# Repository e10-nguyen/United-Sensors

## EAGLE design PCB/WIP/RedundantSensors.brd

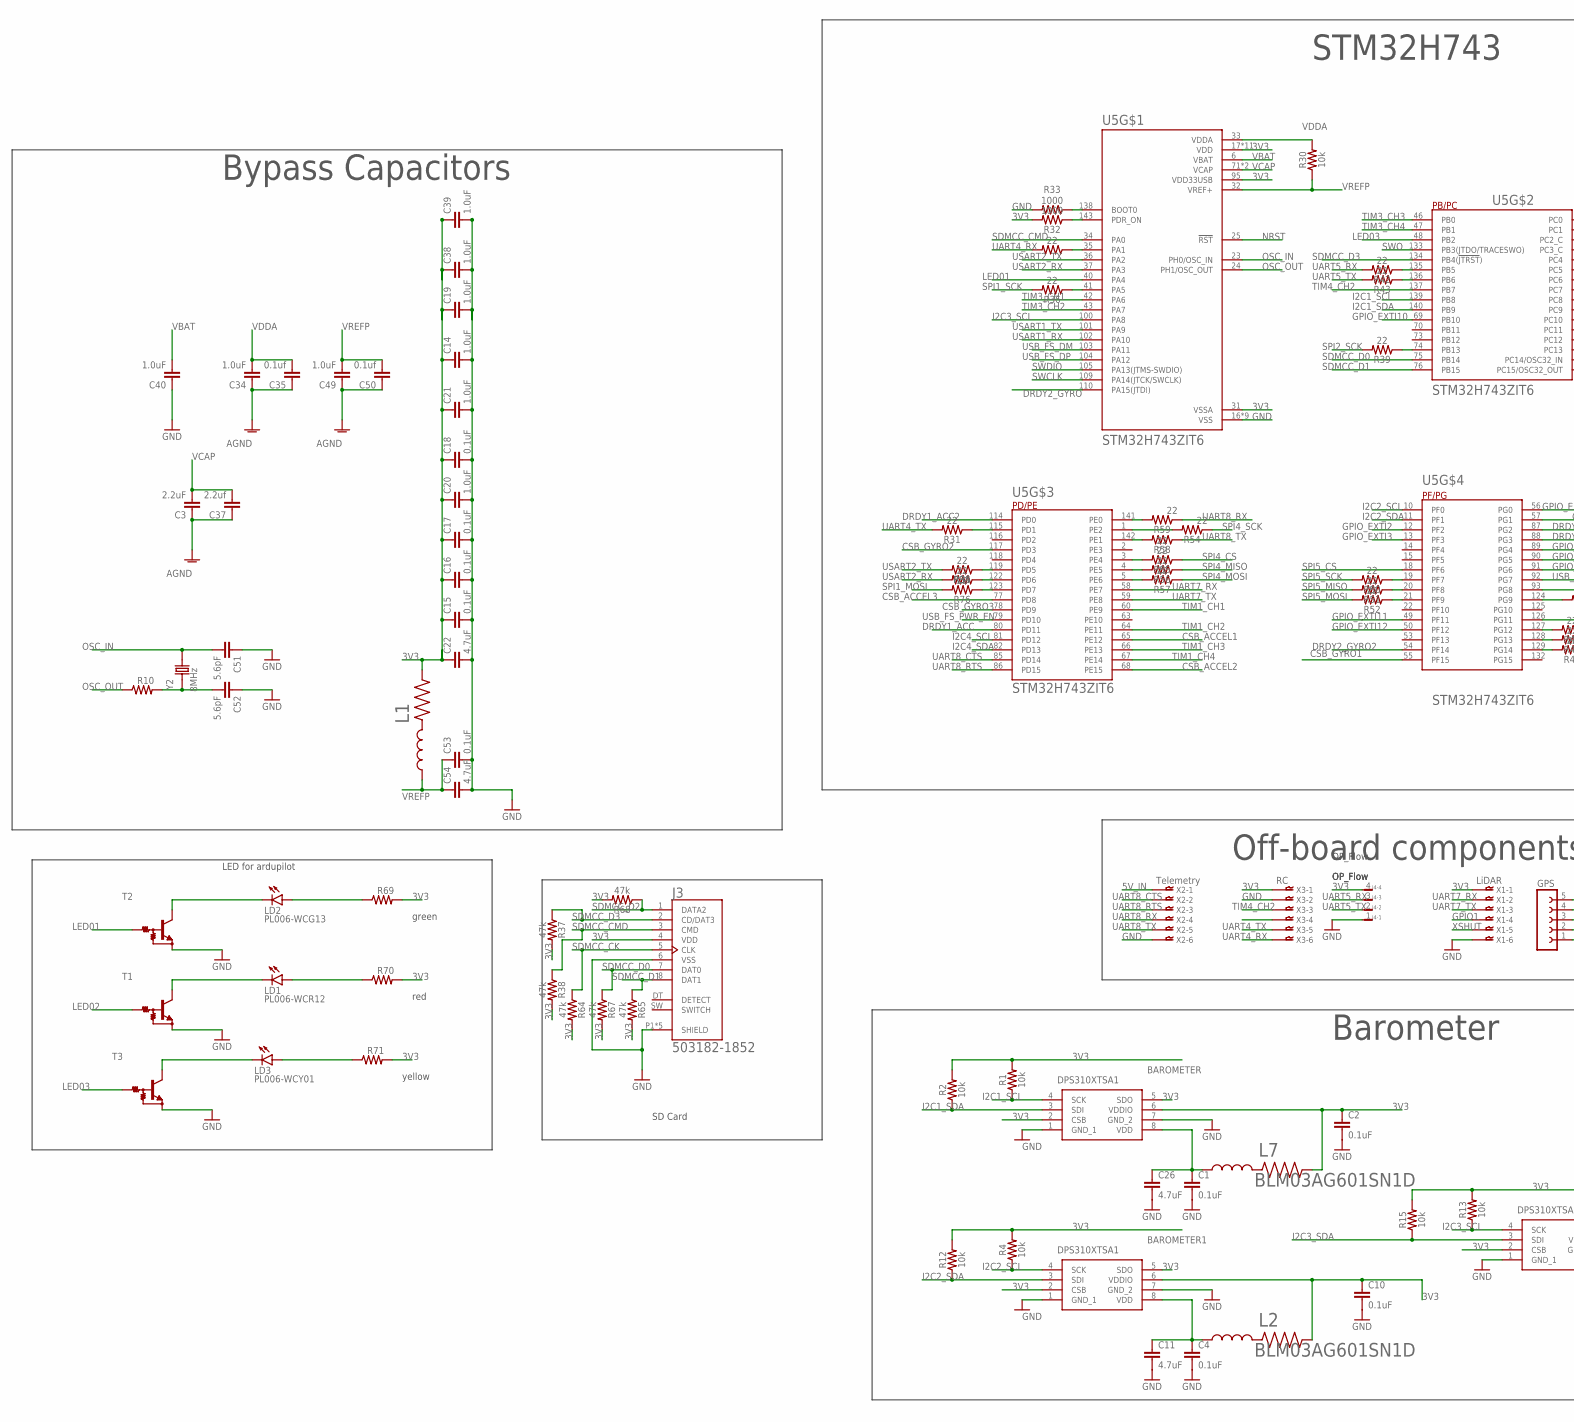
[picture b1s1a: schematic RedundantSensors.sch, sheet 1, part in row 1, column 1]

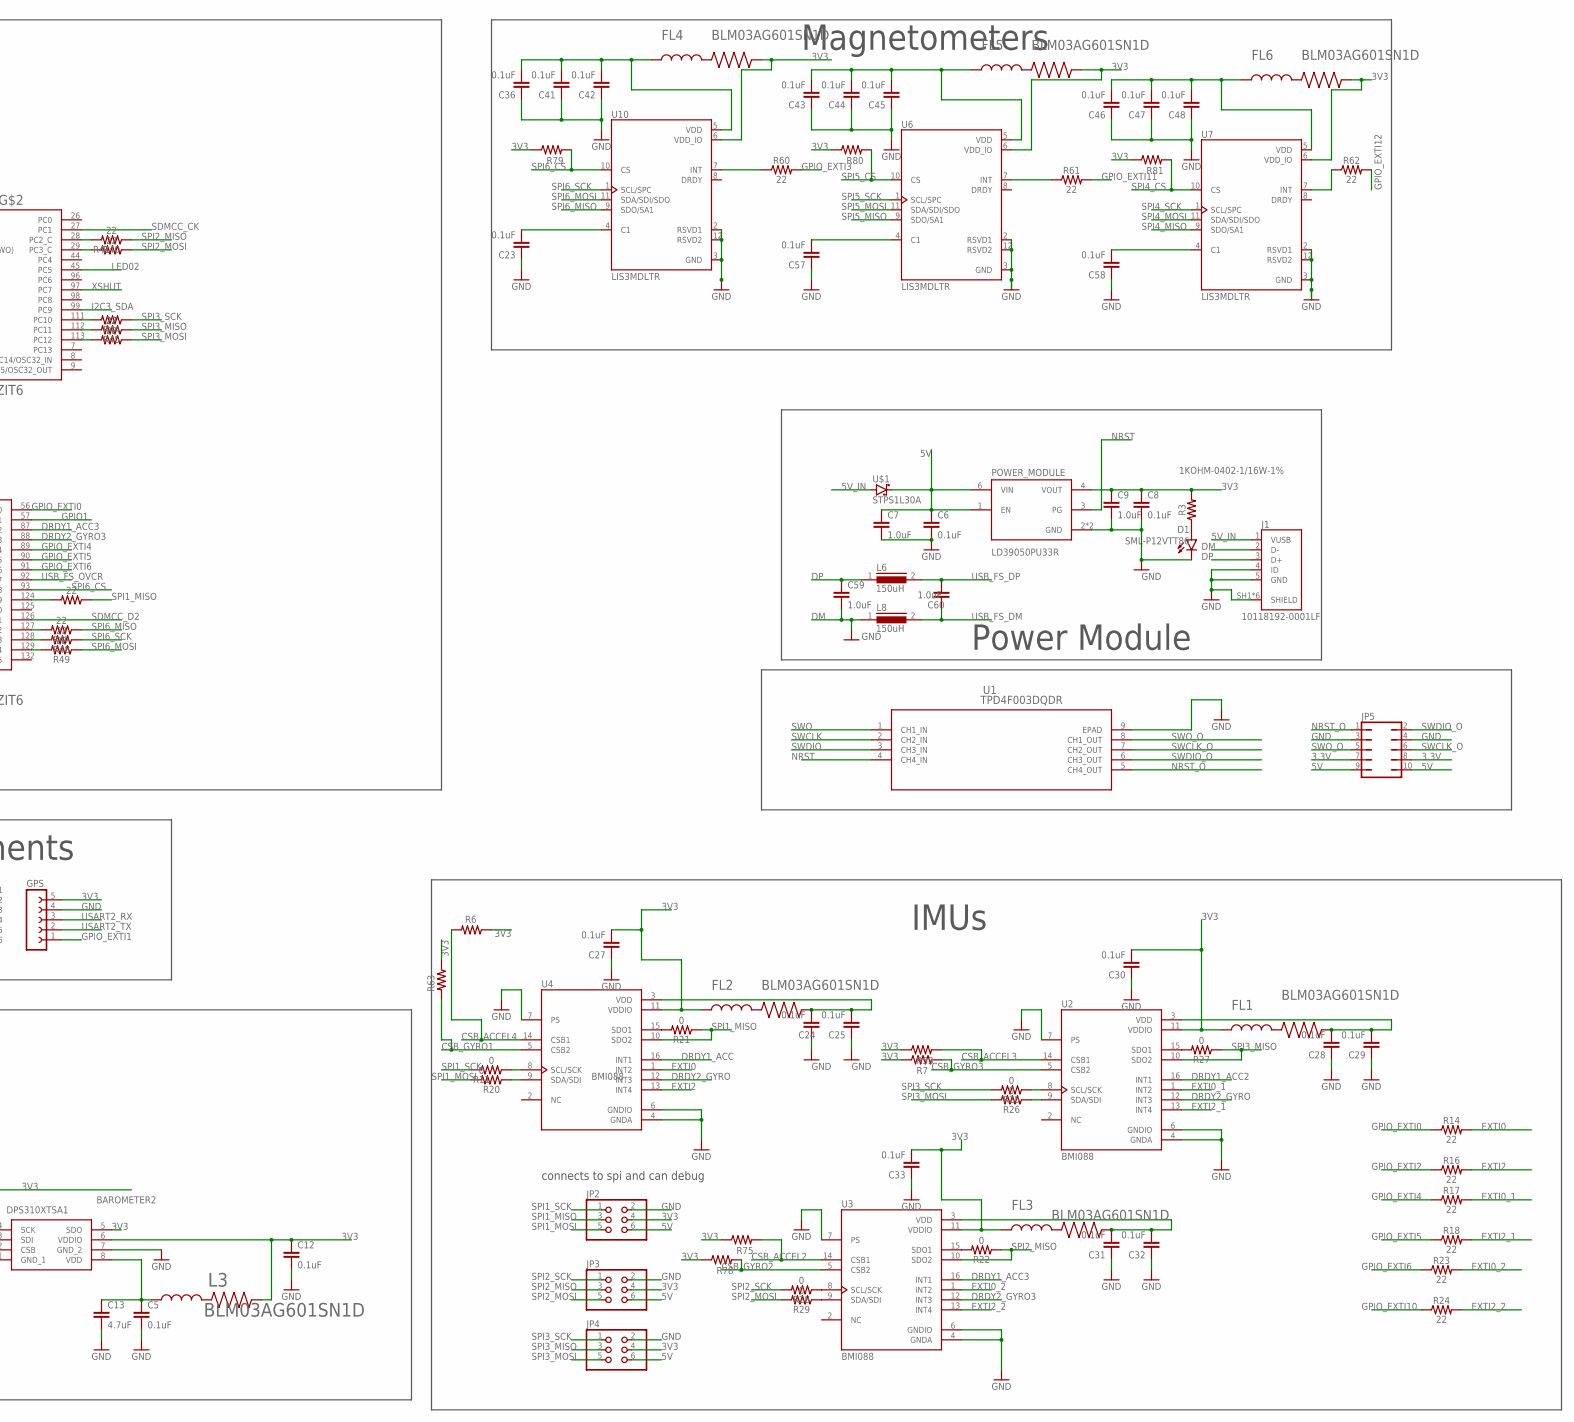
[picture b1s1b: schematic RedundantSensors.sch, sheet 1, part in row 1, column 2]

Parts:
BAROMETER, BAROMETER1, BAROMETER2: DPS310XTSA1
C1, C2, C4, C5, C6, C8, C10, C12: 0.1uF; 0402
C3: 2.2uF; 0805
C7, C9, C59, C60: 1.0uF; 0402
C11, C13, C22, C26, C54: 4.7uF; 0603
C14, C19, C20, C21, C34, C38, C39, C40, C49: 1.0uF; 0805
C15, C16, C17, C18, C23, C24, C25, C27, C28, C29, C30, C31, C32, C33, C36, C41, C42, C43, C44, C45, C46, C47, C48, C53, C57, C58: 0.1uF; 0603
C35, C50: 0.1uf; 0805
C37: 2.2uf; 0805
C51, C52: 5.6pF; 0805
D1: SML-P12VTT86; LED_SML-P11UTT86R
FL1, FL2, FL3, FL4, FL5, FL6: BLM03AG601SN1D; BEADC0603X33N
GPS: FE05-1
J1: 10118192-0001LF; AMPHENOL_10118192-0001LF
J3: 503182-1852; MOLEX_503182-1852
J4: JST-SH-4_SMT_V; BM04B-SRSS-TB
JP2, JP3, JP4: PINHD-2X3; 2X03
JP5: JP5Q
L1, L2, L3, L7: BLM03AG601SN1D; BEADC0603X33N
L6, L8: 150uH; MICC10
LD1: PL006-WCR12; SOT23
LD2: PL006-WCG13; SOT23
LD3: PL006-WCY01; SOT23
POWER_MODULE: LD39050PU33R; SON95P300X300X100-7N
R1, R2, R4, R12, R13, R15, R30: 10k; 0402
R3: 1KOHM-0402-1/16W-1%; 0402
R5, R14, R16, R17, R18, R23, R24, R31, R34, R35, R36, R39, R40, R41, R42, R43, R44, R45, R46, R47, R48, R49, R50, R51, R52, R54, R55, R56, R57, R58, R59, R60, R61, R62, R76, R77: 22; 0402
R6, R7, R53, R63, R75, R78, R79, R80, R81: 10K; RESC1005X35N
R10: 220; RESC1005X35N
R11, R20, R21, R22, R25, R26, R27, R28, R29: 0; 0402
R32, R33: 1000; 0402
R37, R38, R64, R65, R67, R68: 47k; 0402
R69, R70, R71: 270; RESC1005X35N
T1, T2, T3: MUN2213T1-NPN_DRIVER-SC59-BEC; SC59-BEC
U1: TPD4F003DQDR; DQD8_1P2X0P4
U2, U3, U4: BMI088; PQFN50P450X300X100-16N
U5: STM32H743ZIT6; QFP50P2200X2200X160-144N
U6, U7, U10: LIS3MDLTR; XDCR_LIS3MDLTR
U$1: STPS1L30A; DIOM5226X223N
X1: LiDAR; 6FLZ-SM
X2: Telemetry; 6FLZ-SM
X3: RC; 6FLZ-SM
Y2: 8MHz; XTAL_ABLS-8.000MHZ-B2-T

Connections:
3.3V: JP5.7, JP5.8
3V2: C28.2, C29.2, FL1.2, U2.3 (VDD)
3V3: BAROMETER.2 (CSB), BAROMETER.5 (SDO), BAROMETER.6 (VDDIO), BAROMETER1.2 (CSB), BAROMETER1.5 (SDO), BAROMETER1.6 (VDDIO), BAROMETER2.2 (CSB), BAROMETER2.5 (SDO), BAROMETER2.6 (VDDIO), C2.1, C8.1, C9.1, C10.1, C12.1, C14.1, C15.1, C16.1, C17.1, C18.1, C19.1, C20.1, C21.1, C22.1, C27.2, C30.2, C33.2, C38.1, C39.1, FL1.1, FL2.1, FL3.1, FL4.2, FL5.2, FL6.2, GPS.5, J3.4 (VDD), J4.4, JP2.4, JP3.4, JP4.4, L1.2, L2.2, L3.2, L7.2, POWER_MODULE.4 (VOUT), R1.2, R2.2, R3.2, R4.2, R6.1, R7.1, R12.2, R13.2, R15.2, R32.2, R37.2, R38.2, R53.1, R63.1, R64.2, R65.2, R67.2, R68.2, R69.2, R70.2, R71.2, R75.1, R78.1, R79.1, R80.1, R81.1, U2.11 (VDDIO), U3.11 (VDDIO), U4.11 (VDDIO), U5.17 (VDD), U5.30 (VDD), U5.31 (VSSA), U5.39 (VDD), U5.52 (VDD), U5.62 (VDD)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
3V4: C24.2, C25.2, FL2.2, U4.3 (VDD)
3V5: C31.2, C32.2, FL3.2, U3.3 (VDD)
5V: C6.1, C7.1, JP2.6, JP3.6, JP4.6, JP5.9, JP5.10, POWER_MODULE.1 (EN), POWER_MODULE.6 (VIN), U$1.1 (C)
5V_IN: J1.1 (VUSB), U$1.2 (A), X2.1
AGND: C3.1, C34.1, C35.1, C37.1, C49.1, C50.1
CSB_ACCEL1: U5.65 (PE12)
CSB_ACCEL2: R75.2, U3.14 (CSB1), U5.68 (PE15)
CSB_ACCEL3: R53.2, U2.14 (CSB1), U5.77 (PD8)
CSB_ACCEL4: R6.2, U4.14 (CSB1)
CSB_GYRO1: R63.2, U4.5 (CSB2), U5.55 (PF15)
CSB_GYRO2: R78.2, U3.5 (CSB2), U5.117 (PD3)
CSB_GYRO3: R7.2, U2.5 (CSB2), U5.78 (PD9)
DM: C59.2, J1.2 (D-), L8.1
DP: C59.1, J1.3 (D+), L6.1
DRDY1_ACC: U4.16 (INT1), U5.80 (PD11)
DRDY1_ACC2: U2.16 (INT1), U5.114 (PD0)
DRDY1_ACC3: U3.16 (INT1), U5.87 (PG2)
DRDY2_GYRO: U2.12 (INT3), U4.12 (INT3), U5.110 (PA15(JTDI))
DRDY2_GYRO2: U5.54 (PF14)
DRDY2_GYRO3: U3.12 (INT3), U5.88 (PG3)
EXTI0: R14.2, U4.1 (INT2)
EXTI0_1: R17.2, U2.1 (INT2)
EXTI0_2: R23.2, U3.1 (INT2)
EXTI2: R16.2, U4.13 (INT4)
EXTI2_1: R18.2, U2.13 (INT4)
EXTI2_2: R24.2, U3.13 (INT4)
GND: BAROMETER.1 (GND_1), BAROMETER.7 (GND_2), BAROMETER1.1 (GND_1), BAROMETER1.7 (GND_2), BAROMETER2.1 (GND_1), BAROMETER2.7 (GND_2), C1.2, C2.2, C4.2, C5.2, C6.2, C7.2, C8.2, C9.2, C10.2, C11.2, C12.2, C13.2, C14.2, C15.2, C16.2, C17.2, C18.2, C19.2, C20.2, C21.2, C22.2, C23.1, C24.1, C25.1, C26.2, C27.1, C28.1, C29.1, C30.1, C31.1, C32.1, C33.1, C36.1, C38.2, C39.2, C40.1, C41.1, C42.1, C43.1, C44.1, C45.1, C46.1, C47.1, C48.1, C51.1, C52.1, C53.2, C54.2, C57.1, C58.1, D1.C, GPS.4, J1.4 (ID), J1.5 (GND), J1.SH1 (SHIELD), J1.SH2 (SHIELD), J1.SH3 (SHIELD), J1.SH4 (SHIELD), J1.SH5 (SHIELD), J1.SH6 (SHIELD), J3.6 (VSS), J3.P1 (SHIELD), J3.P2 (SHIELD), J3.P3 (SHIELD), J3.P4 (SHIELD), J3.P5 (SHIELD), J4.1, JP2.2, JP3.2, JP4.2, JP5.3, JP5.4, POWER_MODULE.2 (GND), POWER_MODULE.7 (GND)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
GPIO1: U5.57 (PG1), X1.4
GPIO_EXTI0: R14.1, U5.56 (PG0)
GPIO_EXTI1: GPS.1
GPIO_EXTI2: R16.1, U5.12 (PF2)
GPIO_EXTI3: R60.2, U5.13 (PF3)
GPIO_EXTI4: R17.1, U5.89 (PG4)
GPIO_EXTI5: R18.1, U5.90 (PG5)
GPIO_EXTI6: R23.1, U5.91 (PG6)
GPIO_EXTI10: R24.1, U5.69 (PB10)
GPIO_EXTI11: R61.2, U5.49 (PF11)
GPIO_EXTI12: R62.2, U5.50 (PF12)
I2C1_SCL: BAROMETER.4 (SCK), R1.1, U5.139 (PB8)
I2C1_SDA: BAROMETER.3 (SDI), R2.1, U5.140 (PB9)
I2C2_SCL: BAROMETER1.4 (SCK), R4.1, U5.10 (PF0)
I2C2_SDA: BAROMETER1.3 (SDI), R12.1, U5.11 (PF1)
I2C3_SCL: BAROMETER2.4 (SCK), R13.1, U5.100 (PA8)
I2C3_SDA: BAROMETER2.3 (SDI), R15.1, U5.99 (PC9)
I2C4_SCL: U5.81 (PD12)
I2C4_SDA: U5.82 (PD13)
LED01: T2.B, U5.40 (PA4)
LED02: T1.B, U5.45 (PC5)
LED03: T3.B, U5.48 (PB2)
unnamed: BAROMETER2.8 (VDD), C5.1, C13.1, L3.1
unnamed: BAROMETER1.8 (VDD), C4.1, C11.1, L2.1
unnamed: D1.A, R3.1
unnamed: BAROMETER.8 (VDD), C1.1, C26.1, L7.1
unnamed: C52.2, R10.2, Y2.1
unnamed: C23.2, U10.4 (C1)
unnamed: R32.1, U5.143 (PDR_ON)
unnamed: R55.2, U5.3 (PE4)
unnamed: R56.2, U5.4 (PE5)
unnamed: C36.2, C41.2, C42.2, FL4.1, U10.5 (VDD)
unnamed: C57.2, U6.4 (C1)
unnamed: R33.1, U5.138 (BOOT0)
unnamed: R5.1, U5.35 (PA1)
unnamed: R11.1, U4.8 (SCL/SCK)
unnamed: R20.1, U4.9 (SDA/SDI)
unnamed: R40.2, U5.28 (PC2_C)
unnamed: R21.2, U4.15 (SDO1)
unnamed: R22.2, U3.15 (SDO1)
unnamed: R25.1, U2.8 (SCL/SCK)
unnamed: R26.1, U2.9 (SDA/SDI)
unnamed: R27.2, U2.15 (SDO1)
unnamed: R28.1, U3.8 (SCL/SCK)
unnamed: R29.1, U3.9 (SDA/SDI)
unnamed: R34.1, U5.122 (PD6)
unnamed: R35.1, U5.119 (PD5)
unnamed: R36.1, U5.41 (PA5)
unnamed: R39.1, U5.74 (PB13)
unnamed: R41.2, U5.29 (PC3_C)
unnamed: R31.1, U5.115 (PD1)
unnamed: R42.1, U5.135 (PB5)
unnamed: R43.1, U5.136 (PB6)
unnamed: R44.2, U5.111 (PC10)
unnamed: R45.2, U5.112 (PC11)
unnamed: R46.2, U5.113 (PC12)
unnamed: R47.2, U5.127 (PG12)
unnamed: R48.2, U5.128 (PG13)
unnamed: R49.2, U5.129 (PG14)
unnamed: R50.1, U5.19 (PF7)
unnamed: R51.1, U5.20 (PF8)
unnamed: R52.1, U5.21 (PF9)
unnamed: R57.2, U5.5 (PE6)
unnamed: R58.2, U5.142 (PE1)
unnamed: R59.2, U5.141 (PE0)
unnamed: C43.2, C44.2, C45.2, FL5.1, U6.5 (VDD)
unnamed: C58.2, U7.4 (C1)
unnamed: C46.2, C47.2, C48.2, FL6.1, U7.5 (VDD)
unnamed: R60.1, U10.7 (INT)
unnamed: R61.1, U6.7 (INT)
unnamed: R62.1, U7.7 (INT)
unnamed: LD2.3 (C), T2.C
unnamed: LD2.1 (A), R69.1
unnamed: LD1.3 (C), T1.C
unnamed: LD1.1 (A), R70.1
unnamed: LD3.3 (C), T3.C
unnamed: LD3.1 (A), R71.1
unnamed: R54.2, U5.1 (PE2)
unnamed: R76.1, U5.123 (PD7)
unnamed: R77.2, U5.124 (PG9)
NRST: POWER_MODULE.3 (PG), U1.4 (CH4_IN), U5.25 (!RST)
NRST_O: JP5.1, U1.5 (CH4_OUT)
OSC_IN: C51.2, U5.23 (PH0/OSC_IN), Y2.2
OSC_OUT: R10.1, U5.24 (PH1/OSC_OUT)
SDMCC_CK: J3.5 (CLK), R64.1, U5.27 (PC1)
SDMCC_CMD: J3.3 (CMD), R38.1, U5.34 (PA0)
SDMCC_D0: J3.7 (DAT0), R67.1, U5.75 (PB14)
SDMCC_D1: J3.8 (DAT1), R65.1, U5.76 (PB15)
SDMCC_D2: J3.1 (DATA2), R68.1, U5.126 (PG11)
SDMCC_D3: J3.2 (CD/DAT3), R37.1, U5.134 (PB4(!JTRST!))
SPI1_MISO: JP2.3, R21.1, R77.1, U4.10 (SDO2)
SPI1_MOSI: JP2.5, R20.2, R76.2
SPI1_SCK: JP2.1, R11.2, R36.2
SPI2_MISO: JP3.3, R22.1, R40.1, U3.10 (SDO2)
SPI2_MOSI: JP3.5, R29.2, R41.1
SPI2_SCK: JP3.1, R28.2, R39.2
SPI3_MISO: JP4.3, R27.1, R45.1, U2.10 (SDO2)
SPI3_MOSI: JP4.5, R26.2, R46.1
SPI3_SCK: JP4.1, R25.2, R44.1
SPI4_CS: R55.1, R81.2, U7.10 (CS)
SPI4_MISO: R56.1, U7.9 (SDO/SA1)
SPI4_MOSI: R57.1, U7.11 (SDA/SDI/SDO)
SPI4_SCK: R54.1, U7.1 (SCL/SPC)
SPI5_CS: R80.2, U5.18 (PF6), U6.10 (CS)
SPI5_MISO: R51.2, U6.9 (SDO/SA1)
SPI5_MOSI: R52.2, U6.11 (SDA/SDI/SDO)
SPI5_SCK: R50.2, U6.1 (SCL/SPC)
SPI6_CS: R79.2, U5.93 (PG8), U10.10 (CS)
SPI6_MISO: R47.1, U10.9 (SDO/SA1)
SPI6_MOSI: R49.1, U10.11 (SDA/SDI/SDO)
SPI6_SCK: R48.1, U10.1 (SCL/SPC)
SWCLK: U1.2 (CH2_IN), U5.109 (PA14(JTCK/SWCLK))
SWCLK_O: JP5.6, U1.7 (CH2_OUT)
SWDIO: U1.3 (CH3_IN), U5.105 (PA13(JTMS-SWDIO))
SWDIO_O: JP5.2, U1.6 (CH3_OUT)
SWO: U1.1 (CH1_IN), U5.133 (PB3(JTDO/TRACESWO))
SWO_O: JP5.5, U1.8 (CH1_OUT)
TIM1_CH1: U5.60 (PE9)
TIM1_CH2: U5.64 (PE11)
TIM1_CH3: U5.66 (PE13)
TIM1_CH4: U5.67 (PE14)
TIM3_CH1: U5.42 (PA6)
TIM3_CH2: U5.43 (PA7)
TIM3_CH3: U5.46 (PB0)
TIM3_CH4: U5.47 (PB1)
TIM4_CH2: U5.137 (PB7), X3.3
UART4_RX: R5.2, X3.6
UART4_TX: R31.2, X3.5
UART5_RX: J4.3, R42.2
UART5_TX: J4.2, R43.2
UART7_RX: U5.58 (PE7), X1.2
UART7_TX: U5.59 (PE8), X1.3
UART8_CTS: U5.85 (PD14), X2.2
UART8_RTS: U5.86 (PD15), X2.3
UART8_RX: R59.1, X2.4
UART8_TX: R58.1, X2.5
USART1_RX: U5.102 (PA10)
USART1_TX: U5.101 (PA9)
USART2_RX: GPS.3, R34.2, U5.37 (PA3)
USART2_TX: GPS.2, R35.2, U5.36 (PA2)
USB_FS_DM: C60.2, L8.2, U5.103 (PA11)
USB_FS_DP: C60.1, L6.2, U5.104 (PA12)
USB_FS_OVCR: U5.92 (PG7)
USB_FS_PWR_EN: U5.79 (PD10)
VBAT: C40.2, U5.6 (VBAT)
VCAP: C3.2, C37.2, U5.71 (VCAP), U5.106 (VCAP)
VDDA: C34.2, C35.2, R30.2, U5.33 (VDDA)
VREFP: C49.2, C50.2, C53.1, C54.1, L1.1, R30.1, U5.32 (VREF+)
XSHUT: U5.97 (PC7), X1.5

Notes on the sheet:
IMUs
Barometer
Magnetometers
Off-board components
Power Module
STM32H743
Bypass Capacitors
connects to spi and can debug
SD Card
OP_Flow
LED for ardupilot
green
red
yellow

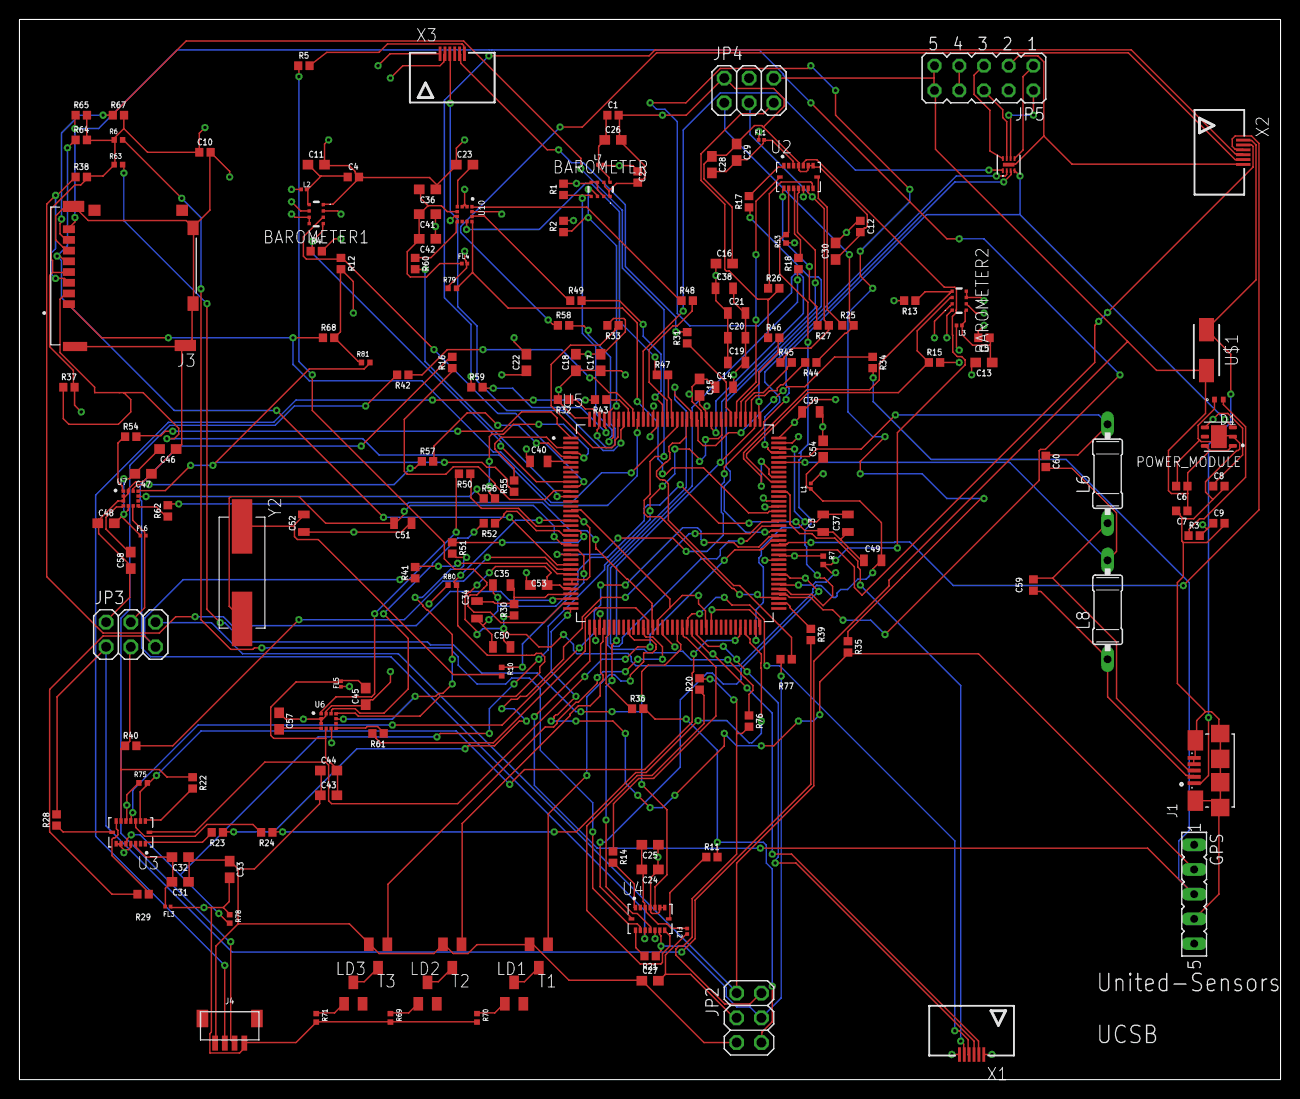
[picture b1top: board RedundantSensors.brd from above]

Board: 4 copper layers, 129.5 x 108.9 mm, 176 parts (0 on the bottom side), 162 nets.

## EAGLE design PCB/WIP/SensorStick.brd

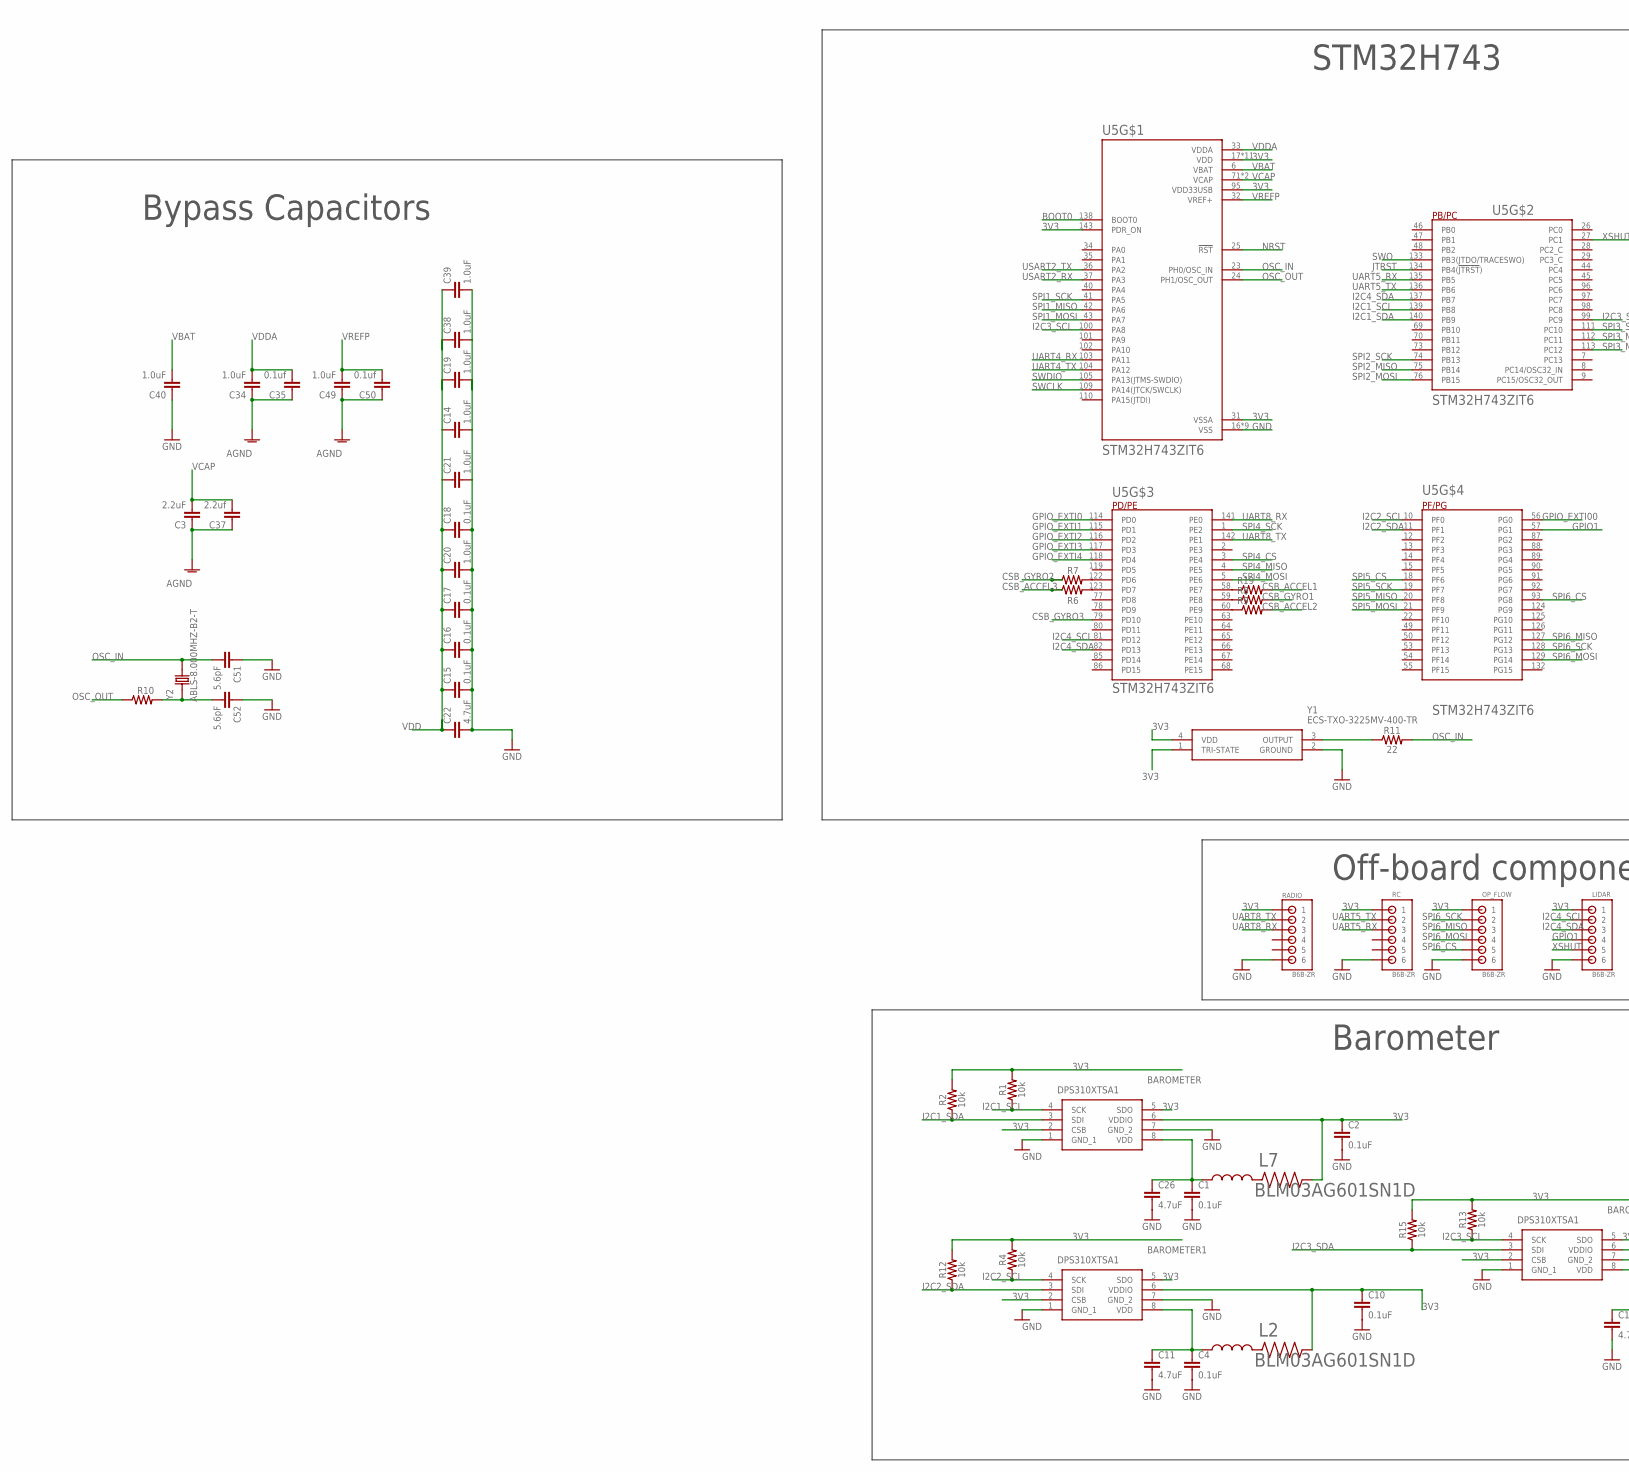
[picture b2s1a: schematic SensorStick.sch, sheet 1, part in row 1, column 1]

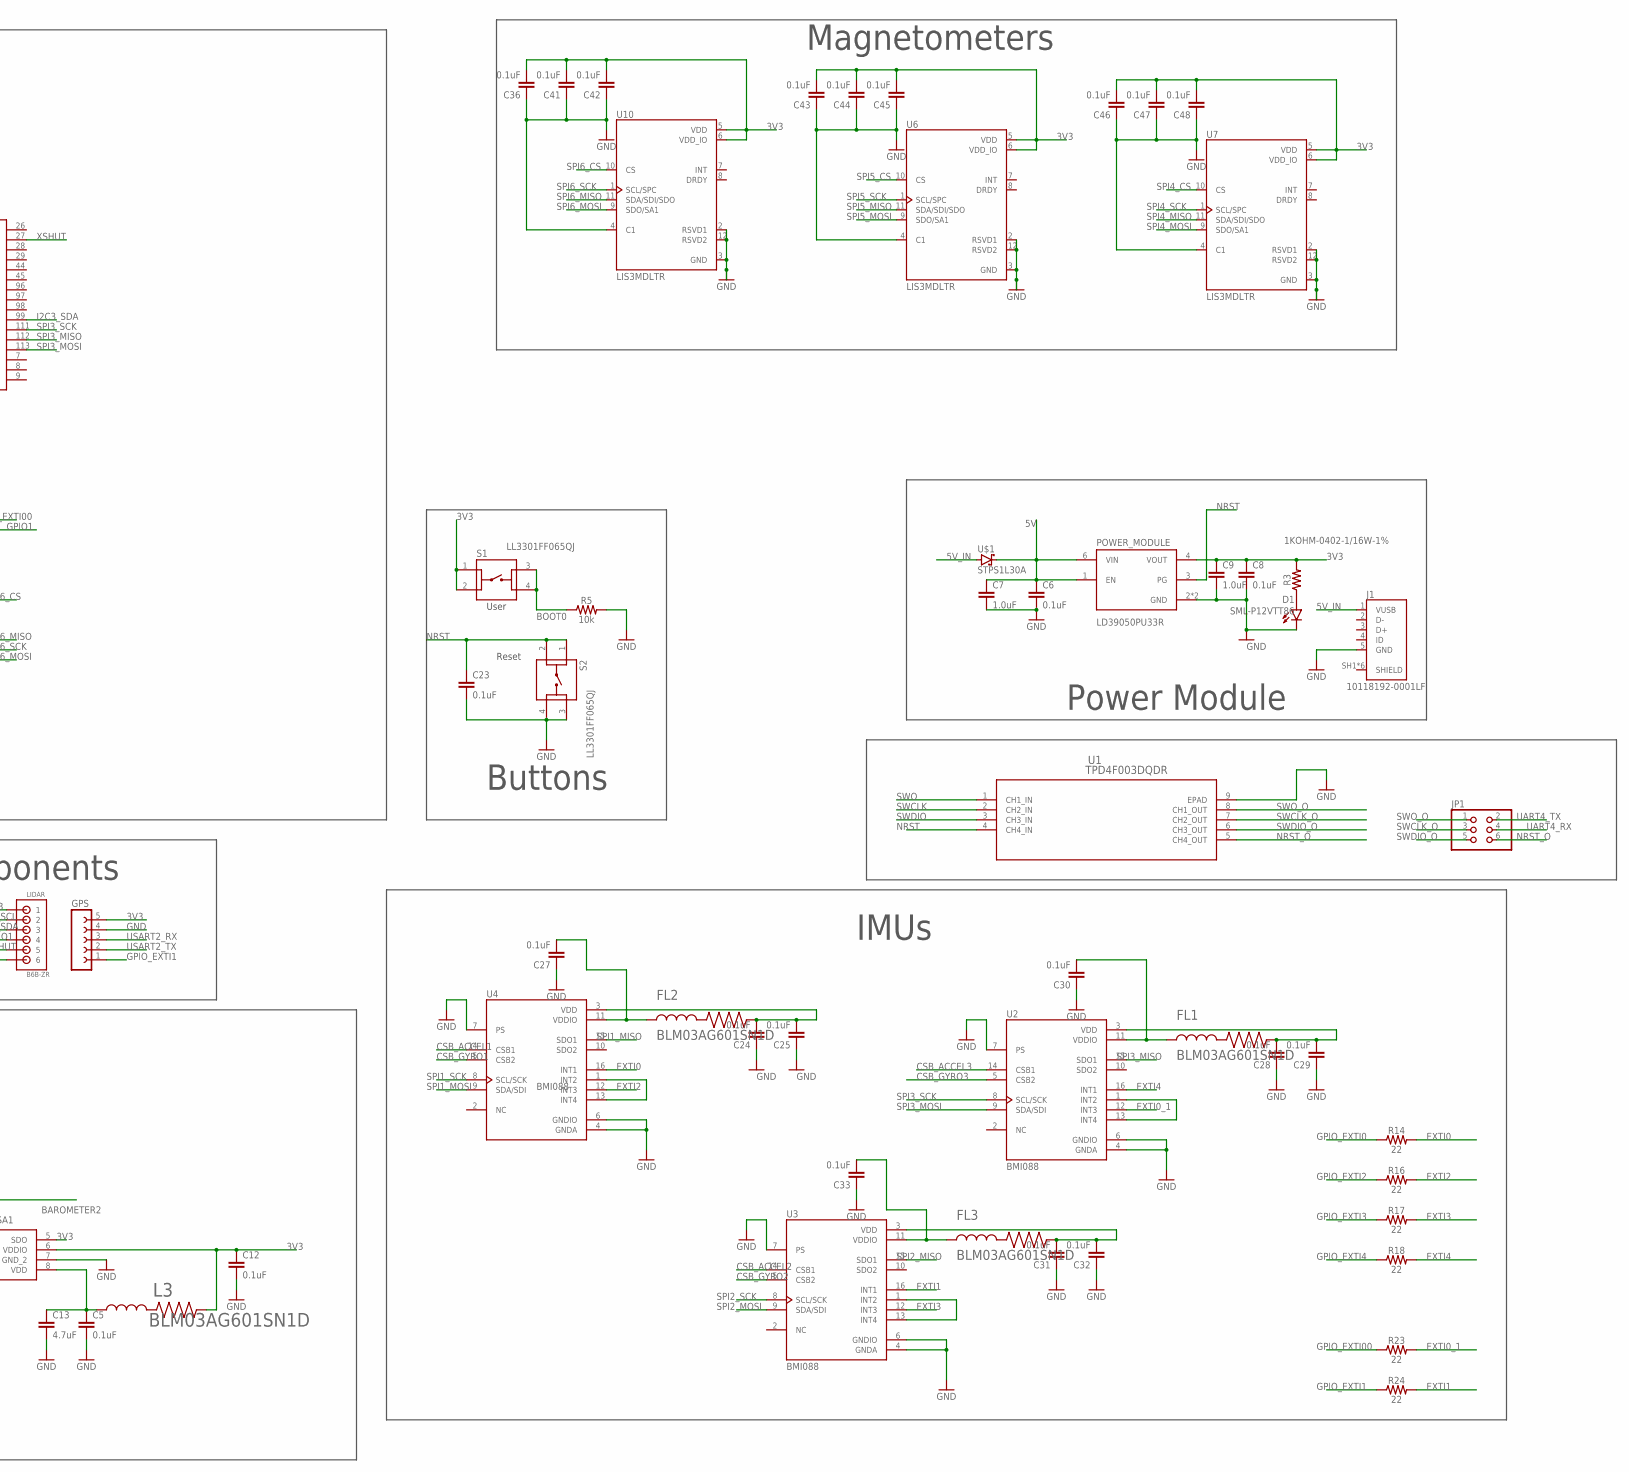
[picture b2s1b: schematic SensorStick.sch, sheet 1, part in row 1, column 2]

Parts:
BAROMETER, BAROMETER1, BAROMETER2: DPS310XTSA1
C1, C2, C4, C5, C6, C8, C10, C12: 0.1uF; 0402
C3: 2.2uF; 0805
C7, C9: 1.0uF; 0402
C11, C13, C22, C26: 4.7uF; 0603
C14, C19, C20, C21, C34, C38, C39, C40, C49: 1.0uF; 0805
C15, C16, C17, C18, C23, C24, C25, C27, C28, C29, C30, C31, C32, C33, C36, C41, C42, C43, C44, C45, C46, C47, C48: 0.1uF; 0603
C35, C50: 0.1uf; 0805
C37: 2.2uf; 0805
C51, C52: 5.6pF; 0805
D1: SML-P12VTT86; LED_SML-P11UTT86R
FL1, FL2, FL3: BLM03AG601SN1D; BEADC0603X33N
GPS: FE05-1
J1: 10118192-0001LF; AMPHENOL_10118192-0001LF
JP1: PINHD-2X3; 2X03
L2, L3, L7: BLM03AG601SN1D; BEADC0603X33N
LIDAR: B6B-ZR
OP_FLOW: B6B-ZR
POWER_MODULE: LD39050PU33R; SON95P300X300X100-7N
R1, R2, R4, R12, R13, R15: 10k; 0402
R3: 1KOHM-0402-1/16W-1%; 0402
R5: 10k; 0603
R6, R7, R8, R9, R19: RT0402FRE07220RL; RESC1005X35N
R10: 220; RESC1005X35N
R11, R14, R16, R17, R18, R23, R24: 22; 0402
RADIO: B6B-ZR
RC: B6B-ZR
S1, S2: LL3301FF065QJ
U1: TPD4F003DQDR; DQD8_1P2X0P4
U2, U3, U4: BMI088; PQFN50P450X300X100-16N
U5: STM32H743ZIT6; QFP50P2200X2200X160-144N
U6, U7, U10: LIS3MDLTR; XDCR_LIS3MDLTR
U$1: STPS1L30A; DIOM5226X223N
Y1: ECS-TXO-3225MV-400-TR; ECSTXO3225MV400TR
Y2: ABLS-8.000MHZ-B2-T; XTAL_ABLS-8.000MHZ-B2-T

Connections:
3V2: C28.2, C29.2, FL1.2, U2.3 (VDD)
3V3: BAROMETER.2 (CSB), BAROMETER.5 (SDO), BAROMETER.6 (VDDIO), BAROMETER1.2 (CSB), BAROMETER1.5 (SDO), BAROMETER1.6 (VDDIO), BAROMETER2.2 (CSB), BAROMETER2.5 (SDO), BAROMETER2.6 (VDDIO), C2.1, C8.1, C9.1, C10.1, C12.1, C36.2, C41.2, C42.2, C43.2, C44.2, C45.2, C46.2, C47.2, C48.2, GPS.5, L2.2, L3.2, L7.2, LIDAR.1, OP_FLOW.1, POWER_MODULE.4 (VOUT), R1.2, R2.2, R3.2, R4.2, R12.2, R13.2, R15.2, RADIO.1, RC.1, S1.1, S1.2, U5.17 (VDD), U5.30 (VDD), U5.31 (VSSA), U5.39 (VDD), U5.52 (VDD), U5.62 (VDD), U5.72 (VDD), U5.84 (VDD), U5.95 (VDD33USB), U5.108 (VDD), U5.121 (VDD), U5.131 (VDD), U5.143 (PDR_ON), U5.144 (VDD), U6.5 (VDD), U6.6 (VDD_IO), U7.5 (VDD), U7.6 (VDD_IO), U10.5 (VDD), U10.6 (VDD_IO), Y1.1 (TRI-STATE), Y1.4 (VDD)
3V4: C24.2, C25.2, FL2.2, U4.3 (VDD)
3V5: C31.2, C32.2, FL3.2, U3.3 (VDD)
5V: C6.1, C7.1, POWER_MODULE.1 (EN), POWER_MODULE.6 (VIN), U$1.1 (C)
5V_IN: J1.1 (VUSB), U$1.2 (A)
AGND: C3.1, C34.1, C35.1, C37.1, C49.1, C50.1
BOOT0: R5.1, S1.3, S1.4, U5.138 (BOOT0)
CSB_ACCEL1: R19.2, U4.14 (CSB1)
CSB_ACCEL2: R9.2, U3.14 (CSB1)
CSB_ACCEL3: R6.1, U2.14 (CSB1)
CSB_GYRO1: R8.2, U4.5 (CSB2)
CSB_GYRO2: R7.1, U3.5 (CSB2)
CSB_GYRO3: U2.5 (CSB2), U5.79 (PD10)
EXTI0: R14.2, U4.16 (INT1)
EXTI0_1: R23.2, U2.12 (INT3)
EXTI1: R24.2, U3.16 (INT1)
EXTI2: R16.2, U4.12 (INT3)
EXTI3: R17.2, U3.12 (INT3)
EXTI4: R18.2, U2.16 (INT1)
GND: BAROMETER.1 (GND_1), BAROMETER.7 (GND_2), BAROMETER1.1 (GND_1), BAROMETER1.7 (GND_2), BAROMETER2.1 (GND_1), BAROMETER2.7 (GND_2), C1.2, C2.2, C4.2, C5.2, C6.2, C7.2, C8.2, C9.2, C10.2, C11.2, C12.2, C13.2, C23.2, C24.1, C25.1, C26.2, C27.1, C28.1, C29.1, C30.1, C31.1, C32.1, C33.1, C36.1, C40.1, C41.1, C42.1, C43.1, C44.1, C45.1, C46.1, C47.1, C48.1, C51.1, C52.1, D1.C, GPS.4, J1.5 (GND), LIDAR.6, OP_FLOW.6, POWER_MODULE.2 (GND), POWER_MODULE.7 (GND), R5.2, S2.3, S2.4, U1.9 (EPAD), U2.4 (GNDA), U2.6 (GNDIO), U2.7 (PS), U3.4 (GNDA), U3.6 (GNDIO), U3.7 (PS), U4.4 (GNDA), U4.6 (GNDIO), U4.7 (PS), U5.16 (VSS), U5.38 (VSS), U5.51 (VSS), U5.61 (VSS), U5.83 (VSS), U5.94 (VSS), U5.107 (VSS), U5.120 (VSS), U5.130 (VSS), U6.2 (RSVD1), U6.3 (GND), U6.4 (C1), U6.12 (RSVD2), U7.2 (RSVD1), U7.3 (GND), U7.4 (C1), U7.12 (RSVD2), U10.2 (RSVD1), U10.3 (GND)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
GND1: C14.2, C15.2, C16.2, C17.2, C18.2, C20.2, C21.2, C22.2
GND2: C19.2
GND3: C38.2
GND4: C39.2
GPIO1: LIDAR.4, U5.57 (PG1)
GPIO_EXTI0: R14.1, U5.114 (PD0)
GPIO_EXTI00: R23.1, U5.56 (PG0)
GPIO_EXTI1: GPS.1, R24.1, U5.115 (PD1)
GPIO_EXTI2: R16.1, U5.116 (PD2)
GPIO_EXTI3: R17.1, U5.117 (PD3)
GPIO_EXTI4: R18.1, U5.118 (PD4)
I2C1_SCL: BAROMETER.4 (SCK), R1.1, U5.139 (PB8)
I2C1_SDA: BAROMETER.3 (SDI), R2.1, U5.140 (PB9)
I2C2_SCL: BAROMETER1.4 (SCK), R4.1, U5.10 (PF0)
I2C2_SDA: BAROMETER1.3 (SDI), R12.1, U5.11 (PF1)
I2C3_SCL: BAROMETER2.4 (SCK), R13.1, U5.100 (PA8)
I2C3_SDA: BAROMETER2.3 (SDI), R15.1, U5.99 (PC9)
I2C4_SCL: LIDAR.2, U5.81 (PD12)
I2C4_SDA: LIDAR.3, U5.82 (PD13), U5.137 (PB7)
IMU_INT3: U3.1 (INT2), U3.13 (INT4)
JTRST: U5.134 (PB4(!JTRST!))
unnamed: R11.1, Y1.3 (OUTPUT)
unnamed: BAROMETER2.8 (VDD), C5.1, C13.1, L3.1
unnamed: BAROMETER1.8 (VDD), C4.1, C11.1, L2.1
unnamed: D1.A, R3.1
unnamed: BAROMETER.8 (VDD), C1.1, C26.1, L7.1
unnamed: C52.2, R10.2, Y2.1
unnamed: C27.2, FL2.1, U4.11 (VDDIO)
unnamed: C30.2, FL1.1, U2.11 (VDDIO)
unnamed: C33.2, FL3.1, U3.11 (VDDIO)
unnamed: R6.2, U5.123 (PD7)
unnamed: R7.2, U5.122 (PD6)
unnamed: R19.1, U5.58 (PE7)
unnamed: R8.1, U5.59 (PE8)
unnamed: R9.1, U5.60 (PE9)
unnamed: RADIO.6, RC.6
unnamed: U4.1 (INT2), U4.13 (INT4)
unnamed: U2.1 (INT2), U2.13 (INT4)
NRST: C23.1, POWER_MODULE.3 (PG), S2.1, S2.2, U1.4 (CH4_IN), U5.25 (!RST)
NRST_O: JP1.6, U1.5 (CH4_OUT)
OSC_IN: C51.2, R11.2, U5.23 (PH0/OSC_IN), Y2.2
OSC_OUT: R10.1, U5.24 (PH1/OSC_OUT)
SPI1_MISO: U4.15 (SDO1), U5.42 (PA6)
SPI1_MOSI: U4.9 (SDA/SDI), U5.43 (PA7)
SPI1_SCK: U4.8 (SCL/SCK), U5.41 (PA5)
SPI2_MISO: U3.15 (SDO1), U5.75 (PB14)
SPI2_MOSI: U3.9 (SDA/SDI), U5.76 (PB15)
SPI2_SCK: U3.8 (SCL/SCK), U5.74 (PB13)
SPI3_MISO: U2.15 (SDO1), U5.112 (PC11)
SPI3_MOSI: U2.9 (SDA/SDI), U5.113 (PC12)
SPI3_SCK: U2.8 (SCL/SCK), U5.111 (PC10)
SPI4_CS: U5.3 (PE4), U7.10 (CS)
SPI4_MISO: U5.4 (PE5), U7.11 (SDA/SDI/SDO)
SPI4_MOSI: U5.5 (PE6), U7.9 (SDO/SA1)
SPI4_SCK: U5.1 (PE2), U7.1 (SCL/SPC)
SPI5_CS: U5.18 (PF6), U6.10 (CS)
SPI5_MISO: U5.20 (PF8), U6.11 (SDA/SDI/SDO)
SPI5_MOSI: U5.21 (PF9), U6.9 (SDO/SA1)
SPI5_SCK: U5.19 (PF7), U6.1 (SCL/SPC)
SPI6_CS: OP_FLOW.5, U5.93 (PG8), U10.10 (CS)
SPI6_MISO: OP_FLOW.3, U5.127 (PG12), U10.11 (SDA/SDI/SDO)
SPI6_MOSI: OP_FLOW.4, U5.129 (PG14), U10.9 (SDO/SA1)
SPI6_SCK: OP_FLOW.2, U5.128 (PG13), U10.1 (SCL/SPC)
SWCLK: U1.2 (CH2_IN), U5.109 (PA14(JTCK/SWCLK))
SWCLK_O: JP1.3, U1.7 (CH2_OUT)
SWDIO: U1.3 (CH3_IN), U5.105 (PA13(JTMS-SWDIO))
SWDIO_O: JP1.5, U1.6 (CH3_OUT)
SWO: U1.1 (CH1_IN), U5.133 (PB3(JTDO/TRACESWO))
SWO_O: JP1.1, U1.8 (CH1_OUT)
UART4_RX: JP1.4, U5.103 (PA11)
UART4_TX: JP1.2, U5.104 (PA12)
UART5_RX: RC.3, U5.135 (PB5)
UART5_TX: RC.2, U5.136 (PB6)
UART8_RX: RADIO.3, U5.141 (PE0)
UART8_TX: RADIO.2, U5.142 (PE1)
USART2_RX: GPS.3, U5.37 (PA3)
USART2_TX: GPS.2, U5.36 (PA2)
VBAT: C40.2, U5.6 (VBAT)
VCAP: C3.2, C37.2, U5.71 (VCAP), U5.106 (VCAP)
VDD: C15.1, C16.1, C17.1, C18.1, C20.1, C21.1, C22.1
VDDA: C34.2, C35.2, U5.33 (VDDA)
VREF1: C14.1
VREF2: C19.1
VREF3: C38.1
VREF4: C39.1
VREFP: C49.2, C50.2, U5.32 (VREF+)
XSHUT: LIDAR.5, U5.27 (PC1)

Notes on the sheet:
IMUs
Barometer
Magnetometers
Off-board components
Buttons
Power Module
STM32H743
Reset
User
Bypass Capacitors

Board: 2 copper layers, 104 parts (0 on the bottom side), 100 nets, no tracks yet.

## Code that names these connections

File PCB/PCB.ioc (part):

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Mcu.Name=STM32H743ZITx
Mcu.Package=LQFP144
Mcu.UserName=STM32H743ZITx
PA0.Mode=Asynchronous
PA0.Signal=UART4_TX
PA1.Mode=RMII
PA1.Signal=ETH_REF_CLK
PA11.Signal=USB_OTG_FS_DM
PA12.Signal=USB_OTG_FS_DP
PA2.Mode=RMII
PA2.Signal=ETH_MDIO
PA3.Mode=Asynchronous
PA3.Signal=USART2_RX
PA5.Mode=Full_Duplex_Master
PA5.Signal=SPI1_SCK
PA6.Mode=Full_Duplex_Master
PA6.Signal=SPI6_MISO
PA7.Mode=RMII
PA7.Signal=ETH_CRS_DV
PA8.Mode=I2C
PA8.Signal=I2C3_SCL
PA9.Signal=I2C3_SMBA
PB0.GPIOParameters=GPIO_Label
PB0.GPIO_Label=LD1 [Green Led]
PB0.Signal=GPIO_Output
PB10.Mode=Full_Duplex_Master
PB10.Signal=SPI2_SCK
PB13.Mode=RMII
PB13.Signal=ETH_TXD1
PB14.GPIOParameters=GPIO_Label
PB14.GPIO_Label=LD3 [Red Led]
PB14.Signal=GPIO_Output
PB2.Mode=Full_Duplex_Master
PB2.Signal=SPI3_MOSI
PB3\ (JTDO/TRACESWO).Mode=Full_Duplex_Master
PB3\ (JTDO/TRACESWO).Signal=SPI6_SCK
PB7.Mode=I2C
PB7.Signal=I2C1_SDA
PB8.Mode=I2C
PB8.Signal=I2C1_SCL
PC1.Mode=RMII
PC1.Signal=ETH_MDC
PC10.Mode=Full_Duplex_Master
PC10.Signal=SPI3_SCK
PC11.Mode=Full_Duplex_Master
PC11.Signal=SPI3_MISO
PC12.Mode=SD_1_bit
PC12.Signal=SDMMC1_CK
PC13.GPIOParameters=GPIO_Label
PC13.GPIO_Label=B1 [Blue PushButton]
PC13.Signal=GPIO_Input
PC14-OSC32_IN\ (OSC32_IN).Mode=LSE-External-Oscillator
PC14-OSC32_IN\ (OSC32_IN).Signal=RCC_OSC32_IN
PC15-OSC32_OUT\ (OSC32_OUT).Mode=LSE-External-Oscillator
PC15-OSC32_OUT\ (OSC32_OUT).Signal=RCC_OSC32_OUT
PC2_C.Mode=Full_Duplex_Master
PC2_C.Signal=SPI2_MISO
PC3_C.Mode=Full_Duplex_Master
PC3_C.Signal=SPI2_MOSI
PC4.Mode=RMII
PC4.Signal=ETH_RXD0
PC5.Mode=RMII
PC5.Signal=ETH_RXD1
PC8.Mode=SD_1_bit
PC8.Signal=SDMMC1_D0
PC9.Mode=I2C
PC9.Signal=I2C3_SDA
PD0.Mode=Asynchronous
PD0.Signal=UART4_RX
PD10.GPIOParameters=GPIO_Label
PD10.GPIO_Label=USB_OTG_FS_PWR_EN
PD10.Signal=GPIO_Output
PD2.Mode=SD_1_bit
PD2.Signal=SDMMC1_CMD
PD5.Mode=Asynchronous
PD5.Signal=USART2_TX
PD7.Mode=Full_Duplex_Master
PD7.Signal=SPI1_MOSI
PD8.GPIOParameters=GPIO_Label
PD8.GPIO_Label=STLINK_RX
PD8.Mode=Asynchronous
PD8.Signal=USART3_TX
PD9.GPIOParameters=GPIO_Label
PD9.GPIO_Label=STLINK_TX
PD9.Mode=Asynchronous
PD9.Signal=USART3_RX
PE1.GPIOParameters=GPIO_Label
PE1.GPIO_Label=LD2 [Yellow Led]
PE1.Signal=GPIO_Output
PE2.Mode=Full_Duplex_Master
PE2.Signal=SPI4_SCK
PE5.Mode=Full_Duplex_Master
PE5.Signal=SPI4_MISO
PE6.Mode=Full_Duplex_Master
PE6.Signal=SPI4_MOSI
PE8.Mode=Asynchronous
PE8.Signal=UART7_TX
PF0.Mode=I2C
PF0.Signal=I2C2_SDA
PF1.Mode=I2C
PF1.Signal=I2C2_SCL
PF14.Mode=I2C
PF14.Signal=I2C4_SCL
PF15.Mode=I2C
PF15.Signal=I2C4_SDA
PF6.Mode=Asynchronous
PF6.Signal=UART7_RX
PF7.Mode=Full_Duplex_Master
PF7.Signal=SPI5_SCK
PF8.Mode=Full_Duplex_Master
PF8.Signal=SPI5_MISO
PF9.Mode=Full_Duplex_Master
PF9.Signal=SPI5_MOSI
PG11.Mode=RMII
PG11.Signal=ETH_TX_EN
PG13.Mode=RMII
PG13.Signal=ETH_TXD0
PG14.Mode=Full_Duplex_Master
PG14.Signal=SPI6_MOSI
PG7.GPIOParameters=GPIO_Label
PG7.GPIO_Label=USB_OTG_FS_OVCR
PG7.Signal=GPXTI7
PG9.Mode=Full_Duplex_Master
PG9.Signal=SPI1_MISO
PH0-OSC_IN\ (PH0).Mode=HSE-External-Clock-Source
PH0-OSC_IN\ (PH0).Signal=RCC_OSC_IN
PH1-OSC_OUT\ (PH1).Signal=RCC_OSC_OUT
RCC.HSE_VALUE=8000000
RCC.SYSCLKFreq_VALUE=64000000
board=NUCLEO-H743ZI2
boardIOC=true

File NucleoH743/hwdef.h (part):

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#define HAL_USE_SPI FALSE
// ADC config
#define HAL_ANALOG_PINS \
{ 16, 16,    3.30/4096 }, /* PA0 BATT_VOLTAGE_SENS */ \
{ 17, 17,    3.30/4096 }, /* PA1 BATT_CURRENT_SENS */ \


// GPIO config
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#define PIN_AFIO_AF(n, v)           ((v) << (((n) % 8U) * 4U))

/* PORTA:
 PA0 BATT_VOLTAGE_SENS ADC1 ADC1_IN16
 PA1 BATT_CURRENT_SENS ADC1 ADC1_IN17
 PA4 MPU_CS CS
 PA5 SPI1_SCK SPI1 AF5
 PA6 SPI1_MISO SPI1 AF5
 PA7 SPI1_MOSI SPI1 AF5
 PA11 OTG_FS_DM OTG1 AF10
 PA12 OTG_FS_DP OTG1 AF10
 PA13 JTMS-SWDIO SWD AF0
 PA14 JTCK-SWCLK SWD AF0
*/

#define VAL_GPIOA_MODER   (PIN_MODE_ANALOG(0U) | \
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
/* PORTB:
 PB0 LED1 OUTPUT
 PB3 SPI3_SCK SPI3 AF6
 PB4 SPI3_MISO SPI3 AF6
 PB5 SPI3_MOSI SPI3 AF7
 PB7 LED2 OUTPUT
*/

#define VAL_GPIOB_MODER   (PIN_MODE_OUTPUT(0U) | \
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                           PIN_AFIO_AF(15U, 0U))

/* PORTC:
 PC7 BARO_CS CS
*/

#define VAL_GPIOC_MODER   (PIN_MODE_INPUT(0U) | \
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                           PIN_AFIO_AF(15U, 0U))

/* PORTE:
 PE8 UART7_TX UART7 AF7
*/

#define VAL_GPIOE_MODER   (PIN_MODE_INPUT(0U) | \
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                           PIN_AFIO_AF(15U, 0U))

/* PORTF:
 PF6 UART7_RX UART7 AF7
*/

#define VAL_GPIOF_MODER   (PIN_MODE_INPUT(0U) | \
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
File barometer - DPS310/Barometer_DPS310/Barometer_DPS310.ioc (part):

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Mcu.Name=STM32L476R(C-E-G)Tx
Mcu.Package=LQFP64
Mcu.UserName=STM32L476RGTx
PA13\ (JTMS-SWDIO).GPIOParameters=GPIO_Label
PA13\ (JTMS-SWDIO).GPIO_Label=TMS
PA13\ (JTMS-SWDIO).Mode=Serial_Wire
PA13\ (JTMS-SWDIO).Signal=SYS_JTMS-SWDIO
PA14\ (JTCK-SWCLK).GPIOParameters=GPIO_Label
PA14\ (JTCK-SWCLK).GPIO_Label=TCK
PA14\ (JTCK-SWCLK).Mode=Serial_Wire
PA14\ (JTCK-SWCLK).Signal=SYS_JTCK-SWCLK
PA2.GPIOParameters=GPIO_Speed,GPIO_PuPd,GPIO_Label,GPIO_Mode
PA2.GPIO_Label=USART_TX
PA2.GPIO_Mode=GPIO_MODE_AF_PP
PA2.GPIO_PuPd=GPIO_NOPULL
PA2.GPIO_Speed=GPIO_SPEED_FREQ_VERY_HIGH
PA2.Mode=Asynchronous
PA2.Signal=USART2_TX
PA3.GPIOParameters=GPIO_Speed,GPIO_PuPd,GPIO_Label,GPIO_Mode
PA3.GPIO_Label=USART_RX
PA3.GPIO_Mode=GPIO_MODE_AF_PP
PA3.GPIO_PuPd=GPIO_NOPULL
PA3.GPIO_Speed=GPIO_SPEED_FREQ_VERY_HIGH
PA3.Mode=Asynchronous
PA3.Signal=USART2_RX
PB3\ (JTDO-TRACESWO).GPIOParameters=GPIO_Label
PB3\ (JTDO-TRACESWO).GPIO_Label=SWO
PB3\ (JTDO-TRACESWO).Signal=SYS_JTDO-SWO
PB6.Signal=GPIO_Output
PB7.Mode=I2C
PB7.Signal=I2C1_SDA
PB8.Mode=I2C
PB8.Signal=I2C1_SCL
PC13.GPIOParameters=GPIO_PuPd,GPIO_Label,GPIO_ModeDefaultEXTI
PC13.GPIO_Label=B1 [Blue PushButton]
PC13.GPIO_ModeDefaultEXTI=GPIO_MODE_IT_FALLING
PC13.GPIO_PuPd=GPIO_NOPULL
PC13.Signal=GPXTI13
PC14-OSC32_IN\ (PC14).Mode=LSE-External-Oscillator
PC14-OSC32_IN\ (PC14).Signal=RCC_OSC32_IN
PC15-OSC32_OUT\ (PC15).Mode=LSE-External-Oscillator
PC15-OSC32_OUT\ (PC15).Signal=RCC_OSC32_OUT
PH0-OSC_IN\ (PH0).Signal=RCC_OSC_IN
PH1-OSC_OUT\ (PH1).Signal=RCC_OSC_OUT
RCC.HSE_VALUE=8000000
RCC.SYSCLKFreq_VALUE=80000000
RCC.SYSCLKSource=RCC_SYSCLKSOURCE_PLLCLK
board=NUCLEO-L476RG
boardIOC=true

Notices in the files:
parts and their libraries:
SparkFun-Capacitors: Licensing: Creative Commons ShareAlike 4.0 International - https://creativecommons.org/licenses/by-sa/4.0
COPYRIGHT: Copyright (C) 2023 Ultra Librarian. All rights reserved.
